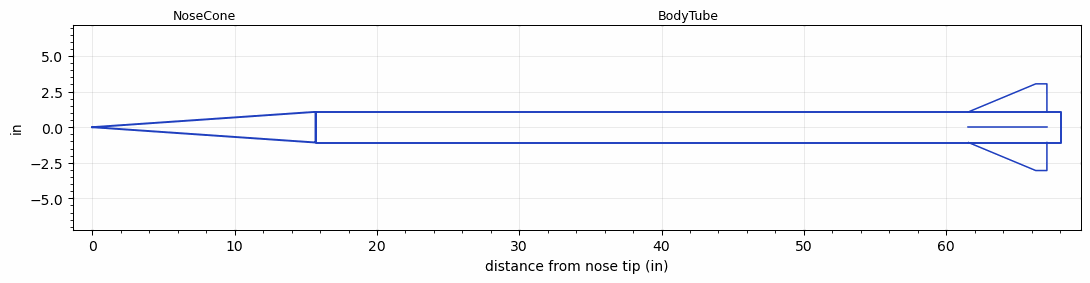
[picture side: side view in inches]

<RASAeroDocument>
 <FileVersion>2</FileVersion>
 <RocketDesign>
  <NoseCone>
   <Length>15.681</Length>
   <Diameter>2.154</Diameter>
   <Shape>Conical</Shape>
   <Location>0</Location>
  </NoseCone>
  <BodyTube>
   <Length>52.4</Length>
   <Diameter>2.154</Diameter>
   <Location>15.681</Location>
   <Fin>
    <Count>4</Count>
    <Chord>5.512</Chord>
    <Span>1.969</Span>
    <SweepDistance>4.724</SweepDistance>
    <TipChord>0.787</TipChord>
    <Thickness>0.098</Thickness>
    <LERadius>0.01</LERadius>
    <Location>6.512</Location>
    <AirfoilSection>Hexagonal</AirfoilSection>
    <FX1>0.2</FX1>
    <FX3>0.2</FX3>
   </Fin>
  </BodyTube>
  <Surface>Rough Camouflage Paint</Surface>
  <ModifiedBarrowman>True</ModifiedBarrowman>
  <Turbulence>True</Turbulence>
  <UseBooster1>False</UseBooster1>
  <UseBooster2>False</UseBooster2>
 </RocketDesign>
 <LaunchSite>
  <Altitude>800</Altitude>
  <Pressure>0</Pressure>
  <RodAngle>0</RodAngle>
  <RodLength>4</RodLength>
  <Temperature>50</Temperature>
  <WindSpeed>0</WindSpeed>
 </LaunchSite>
 <Recovery>
  <Altitude1>1000</Altitude1>
  <Altitude2>1000</Altitude2>
  <DeviceType1>None</DeviceType1>
  <DeviceType2>None</DeviceType2>
  <Event1>False</Event1>
  <Event2>False</Event2>
  <Size1>1</Size1>
  <Size2>1</Size2>
  <EventType1>None</EventType1>
  <EventType2>None</EventType2>
  <CD1>1.33</CD1>
  <CD2>1.33</CD2>
 </Recovery>
 <SimulationList>
  <Simulation>
   <SustainerEngine>L2050LW  (LR)</SustainerEngine>
   <SustainerLaunchWt>11.2</SustainerLaunchWt>
   <SustainerCG>42.13</SustainerCG>
   <SustainerIgnitionDelay>0</SustainerIgnitionDelay>
   <Booster1SeparationDelay>0</Booster1SeparationDelay>
   <Booster1IgnitionDelay>0</Booster1IgnitionDelay>
   <IncludeBooster1>False</IncludeBooster1>
   <Booster2Delay>0</Booster2Delay>
   <IncludeBooster2>False</IncludeBooster2>
   <TimetoApogee>33.09045</TimetoApogee>
   <MaxAltitude>28917.22</MaxAltitude>
   <MaxVelocity>3298.328</MaxVelocity>
  </Simulation>
  <Simulation>
   <SustainerEngine>M1378LR  (Loki)</SustainerEngine>
   <SustainerLaunchWt>11.8</SustainerLaunchWt>
   <SustainerCG>42.13</SustainerCG>
   <SustainerIgnitionDelay>0</SustainerIgnitionDelay>
   <Booster1SeparationDelay>0</Booster1SeparationDelay>
   <Booster1IgnitionDelay>0</Booster1IgnitionDelay>
   <IncludeBooster1>False</IncludeBooster1>
   <Booster2Delay>0</Booster2Delay>
   <IncludeBooster2>False</IncludeBooster2>
   <TimetoApogee>36.00996</TimetoApogee>
   <MaxAltitude>33381.68</MaxAltitude>
   <MaxVelocity>3193.5</MaxVelocity>
  </Simulation>
 </SimulationList>
</RASAeroDocument>
